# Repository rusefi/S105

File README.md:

# S105

Reverse engineering of SOATE S105 396200-3763010-00 ECU using KiCad EDA

[TL,DR: schematics (see open issues)](hardware/s105/s105.pdf)

[Interactive Pinout](https://rusefi.com/docs/pinouts/s105/)

Geehy apm32F407VGT7

[Forum Discussion](https://rusefi.com/forum/viewtopic.php?f=4&t=2496)

https://www.youtube.com/watch?v=v7S3eSeuTio

Alternative unofficial firmware https://github.com/rusefi/rusefi/tree/master/firmware/config/boards/s105

Binary https://rusefi.com/build_server/rusefi_bundle_s105.zip

See also https://github.com/rusefi/m74.9

[rusefi-status.md](rusefi-status.md)

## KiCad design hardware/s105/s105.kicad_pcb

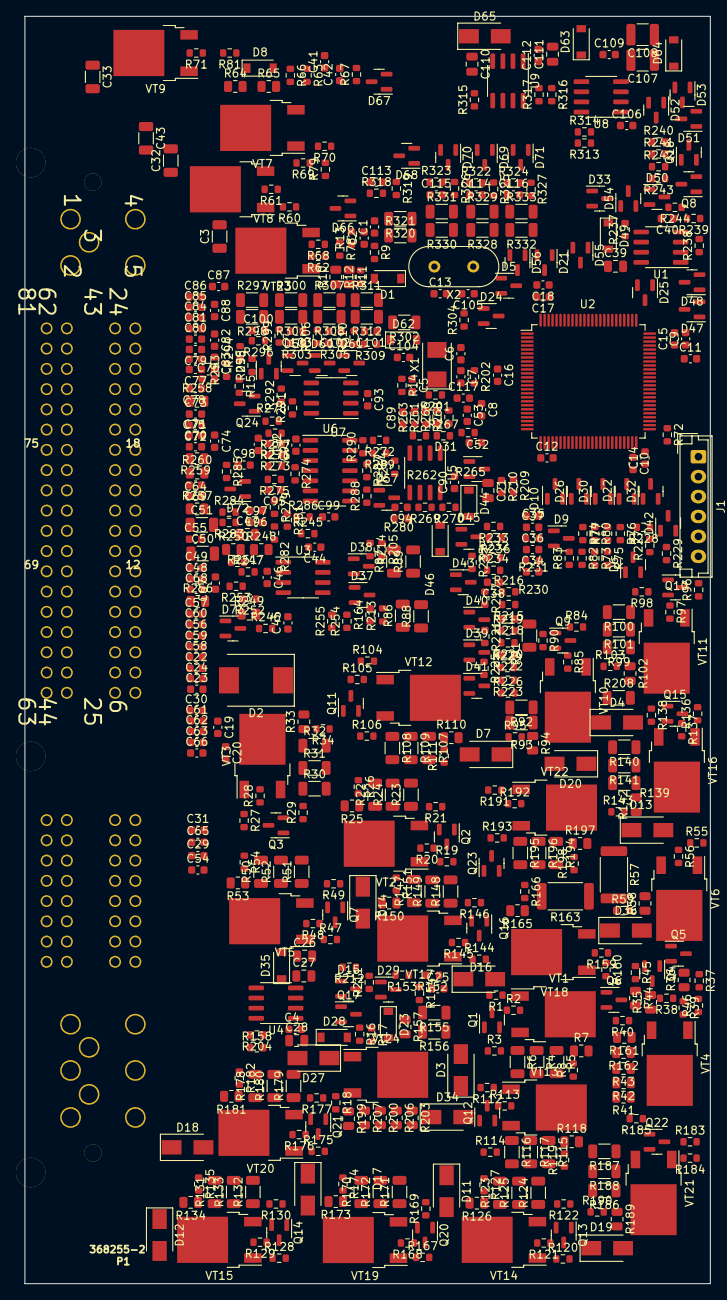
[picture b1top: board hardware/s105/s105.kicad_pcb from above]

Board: 2 copper layers, 86.0 x 159.0 mm, 583 parts (0 on the bottom side), 262 nets, no tracks yet.

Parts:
C1, C2, C41, C42: C_0603_1608Metric
C3, C32, C33, C43: C_Small; C_1206_3216Metric
C4, C19, C20, C22, C23, C24, C25, C29, C30, C31, C40, C44, C45, C46, C49, C54, C55, C56, C57, C58, C59, C60, C61, C62, C63, C64, C65, C66, C67, C68, C70, C71, C84, C85, C86, C87, C89, C90, C91, C92, C93, C94, C95, C96, C97, C98, C99, C100, C106, C109, C112: C0603; C_0603_1608Metric
C5: 10nF; C_0603_1608Metric
C6, C7: 18pF; C_0603_1608Metric
C8, C12: 1uF; C_0603_1608Metric
C9, C14, C15, C16, C17, C18, C34, C35, C36, C37, C38, C48, C52, C53, C69, C72, C73, C74, C75, C76, C77, C78, C79, C80, C81, C82, C83, C88, C101, C104, C113, C114, C115, C116, C117: 100nF; C_0603_1608Metric
C10, C11: 2.2uF; C_0603_1608Metric
C13, C102, C103, C105: NM; C_0603_1608Metric
C21, C26, C27, C28, C39, C47, C110, C111: C0805; C_0805_2012Metric
C50, C51: C1206; C_1206_3216Metric
C107, C108: C1210; C_1210_3225Metric
D1, D8, D23, D28, D44, D46: 1N4148W; D_SOD-123
D2: .; D_SMC
D3: NM; D_SMA
D4, D7, D11, D12, D13, D14, D16, D17, D18, D19, D20, D27, D34, D36, D65: .; D_SMA
D5, D6, D9, D10, D15, D21, D22, D24, D25, D26, D29, D30, D31, D32, D33, D37, D38, D39, D40, D41, D42, D43, D45, D47, D48, D50, D51, D52, D53, D54, D55, D56, D57, D58, D59, D60, D61, D66, D67, D68, D69, D70, D71, D72: BAV99; SOT-23
D35, D49, D63, D64: .; D_SOD-123
D62: NM; D_SOD-123
D73: .; SOT-23
J1: Conn_01x06; JST_EH_B6B-EH-A_1x06_P2.50mm_Vertical
P1: 368255-2
Q1, Q2, Q3, Q6, Q7, Q8, Q9, Q10, Q11, Q12, Q13, Q14, Q15, Q16, Q17, Q18, Q20, Q21, Q22, Q23: BC847C; SOT-23
Q4, Q5, Q24: .; SOT-23
R1, R2, R12, R16, R17, R19, R20, R27, R28, R37, R39, R46, R47, R48, R55, R56, R66, R84, R85, R96, R97, R104, R105, R112, R113, R120, R121, R128, R129, R136, R137, R144, R145, R159, R160, R167, R168, R175, R176, R183, R184, R191, R192: 3K; R_0603_1608Metric
R3, R18, R21, R29, R40, R49, R90, R98, R106, R114, R122, R130, R138, R146, R169, R177, R185, R193: 360R; R_0603_1608Metric
R4, R5, R6, R22, R23, R24, R30, R31, R32, R50, R51, R52, R91, R92, R93, R99, R100, R101, R107, R108, R109, R115, R116, R117, R123, R124, R125, R131, R132, R133, R139, R140, R141, R147, R148, R149, R170, R171, R172, R178, R179, R180, R186, R187, R188, R194, R195, R196: 1R; R_1206_3216Metric
R7, R25, R33, R44, R53, R58, R94, R102, R110, R118, R126, R134, R142, R150, R165, R173, R181, R189, R197: 82K; R_0805_2012Metric
R8, R15, R26, R34, R45, R54, R59, R95, R103, R111, R119, R127, R135, R143, R151, R166, R174, R182, R190, R198: 51K; R_0603_1608Metric
R9, R63: 8K2; R_0603_1608Metric
R10, R11, R64, R65: 10K; R_0805_2012Metric
R13, R67: 6K8; R_0603_1608Metric
R14: 10K; R_0603_1608Metric
R35: 6.8k; R_0805_2012Metric
R36: 2.2k; R_0805_2012Metric
R38: 18K; R_0603_1608Metric
R41, R42, R43, R161, R162, R199, R200, R203, R206, R207: 10R; R_0805_2012Metric
R57, R163: 50k?; R_2512_6332Metric
R60, R62, R69, R78, R79, R81: 10; R_0603_1608Metric
R61, R71, R80, R153, R204, R233, R236: 100; R_0603_1608Metric
R68, R70, R73, R74, R75, R82, R83, R212, R216, R219, R223, R224, R225, R226, R227, R228, R229, R232, R234, R235, R238, R255, R261, R293, R299, R304, R306, R313, R314, R326: NM; R_0603_1608Metric
R72, R211, R215, R220, R269, R272, R273, R276, R278, R279, R317: 1k; R_0603_1608Metric
R76: 22K; R_0603_1608Metric
R77: 510K; R_0603_1608Metric
R86, R87, R88, R89: 3k; R_1206_3216Metric
R152, R210: 6.8k; R_0603_1608Metric
R154, R209: 68k; R_0603_1608Metric
R155, R156, R208, R298, R311, R320, R329, R332: 4.7k; R_1206_3216Metric
R157, R248, R249, R250: 10k; R_0805_2012Metric
R158, R239, R245, R247, R251, R252, R253, R254, R295, R315, R316: 4.7k; R_0603_1608Metric
R164, R205, R213, R214, R217, R221, R237, R274, R275, R277, R285, R286, R287, R288, R289, R290: 22k; R_0603_1608Metric
R201, R230, R231, R263: 3k; R_0603_1608Metric
R202, R264, R280, R283, R303, R305, R323: 300; R_0603_1608Metric
R218, R222, R271: 6k; R_0603_1608Metric
R240, R241: 47; R_0603_1608Metric
R242, R284, R294, R310, R319, R325, R327: 51k; R_0603_1608Metric
R243, R244, R296, R309, R318, R322, R324: 33k; R_0603_1608Metric
R246: 82k; R_0603_1608Metric
R256, R257, R258, R259, R260: 0; R_0805_2012Metric
R262, R265, R266, R267, R268, R270: MN; R_0603_1608Metric
R281, R282: 18k; R_0603_1608Metric
R291, R292: 62; R_0603_1608Metric
R297, R300, R301, R302, R307, R308, R312, R321, R328, R330, R331, R333: NM; R_1206_3216Metric
U1, U4, U5, U8, U9: case only; SOIC-8_3.9x4.9mm_P1.27mm
U2: STM32F427VGT6; LQFP-100_14x14mm_P0.5mm
U3: LM2903; SOIC-8_3.9x4.9mm_P1.27mm
U6: LM2902; SO-14_3.9x8.65mm_P1.27mm
U7: SIT1042T/3; SOIC-8_3.9x4.9mm_P1.27mm
VT1, VT2, VT3, VT4, VT5, VT6, VT10, VT11, VT12, VT13, VT14, VT15, VT16, VT17, VT18, VT19, VT20, VT21, VT22, VT24: IRLR3110Z; TO-252-2
VT7, VT8, VT9, VT23: ISL9V3040D3S; TO-252-2
X1: 8MHz 20pF; Crystal_SMD_5032-2Pin_5.0x3.2mm
X2: NM; Crystal_HC49-U_Vertical

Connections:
+3.3V: C8.2, C9.2, C12.2, C14.2, C15.2, C16.2, C17.2, C18.2, C106.1, C107.1, C108.1, D5.2 (A), D6.2 (A), D9.2 (A), D10.2 (A), D21.2 (A), D22.2 (A), D24.2 (A), D25.2 (A), D26.2 (A), D29.2 (A), D30.2 (A), D31.2 (A), D32.2 (A), D33.2 (A), D37.2 (A), D38.2 (A), D39.2 (A), D40.2 (A), D41.2 (A), D42.2 (A), D43.2 (A), D44.1 (K), D45.2 (A), D46.1 (K), D47.2 (A), D48.2 (A), D50.2 (A), D51.2 (A), D52.2 (A), D53.2 (A), D54.2 (A), D55.2 (A), D56.2 (A), D58.2 (A), D59.2 (A), D60.2 (A), D61.2 (A), D64.1 (K), D66.2 (A), D67.2 (A), D68.2 (A), D69.2 (A), D70.2 (A), D71.2 (A), J1.4, R14.1, R86.2, R87.1, R88.2, R89.1, R229.2, R244.2, R265.1, R270.1, R313.1, U2.11 (VDD), U2.19 (VDD), U2.21 (VREF+), U2.22 (VDDA), U2.28 (VDD), U2.50 (VDD), U2.75 (VDD), U2.100 (VDD), U7.5 (VREF), U8.1 (BOOT)
+5V: C4.1, C28.1, C40.1, C44.1, C90.1, C93.1, D27.2 (A), D72.2 (A), R1.2, R19.2, R27.2, R46.1, R47.2, R55.2, R60.1, R78.1, R79.1, R81.1, R84.2, R96.2, R104.2, R112.2, R120.2, R128.2, R136.2, R144.2, R154.2, R155.2, R156.2, R157.2, R158.2, R159.2, R167.2, R175.2, R183.2, R191.2, R238.2, R245.2, R251.1, R271.2, R274.1, U1.3 (GND), U3.8 (V+), U4.1 (BOOT), U5.8 (PHASE), U6.4 (V+), U7.3 (VCC)
+5VD: C87.1, C111.1, C112.1, P1.32, P1.33, R74.1, R80.1, R216.2, R219.2, R224.2, R232.2, R236.1, R316.1, U9.1 (BOOT)
+12V: C19.1, C20.1, C26.1, C39.1, D1.1 (K), D2.2 (A), D3.2 (A), D4.1 (K), D7.1 (K), D8.1 (K), D11.1 (K), D12.1 (K), D13.1 (K), D14.1 (K), D16.1 (K), D17.1 (K), D18.1 (K), D19.1 (K), D20.1 (K), D35.2 (A), D36.1 (K), D49.2 (A), D63.2 (A), D65.2 (A), P1.44, P1.45, P1.63, R208.1, R297.2, R300.2, R307.2, R311.2, R320.2, R328.2, R330.2, R332.2, U1.7 (COMP/DIS/OC)
/AC_Press: C76.2, P1.21, R223.2, R224.1, R225.1
/AC_Relay: C66.1, D18.2 (A), P1.69, R181.2, VT20.2 (D)
/AFR_1: C70.1, P1.18, R76.1, R77.2, R228.2
/AFR_1_Heater: C29.1, D16.2 (A), P1.48, R165.2, VT18.2 (D)
/AFR_2: C64.1, P1.55, R82.2, R83.1, R227.1
/Absorber: C63.1, D14.2 (A), P1.46, R150.2, VT17.2 (D)
/Atart_dis_Relay: C62.1, D13.2 (A), P1.50, R142.2, VT16.2 (D)
/BOOT0: R15.1, R293.1, U2.94 (BOOT0)
/CAM_in: C88.2, P1.79, R299.2, R300.1, R301.2
/CAN_H: C84.1, P1.62, Q24.1 (B), R291.1, U7.7 (CANH)
/CAN_L: C85.1, P1.81, Q24.2 (E), R292.2, U7.6 (CANL)
/CEL: C68.1, D20.2 (A), P1.31, R197.2, VT22.2 (D)
/CLT: C75.2, P1.39, R87.2, R89.2, R205.1, R214.1
/Crank_Sens+: C47.1, C51.1, P1.15, R249.1, R250.1
/Crank_Sens-: C47.2, C50.1, P1.34, R248.1, R250.2
/DCNS: C73.2, P1.75, R306.2, R307.1, R308.2
/DIN1: C80.2, P1.72, R319.2, R320.1, R321.2
/DIN5: C83.2, P1.76, R327.2, R332.1, R333.2
/DPH2: C81.2, P1.73, R326.2, R330.1, R331.2
/ECO/CLT_Out: C57.1, D4.2 (A), P1.10, R102.2, R208.2, VT11.2 (D)
/Fan_Relay_1: C65.1, D17.2 (A), P1.68, R173.2, VT19.2 (D)
/Fan_relay_2/Unk_Out_2: C67.1, D19.2 (A), P1.30, R189.2, VT21.2 (D)
/Fuel_Pump_Relay: C61.1, D12.2 (A), P1.70, R134.2, VT15.2 (D)
/GNDA: P1.17, P1.20, P1.35, P1.36, P1.51, P1.52, P1.53, P1.54, R256.1, R257.1, R258.1, R259.1, R260.1
/IAT: C77.2, P1.40, R86.1, R88.1, R164.1, R213.1
/IGN_1: C3.1, P1.5, R10.1, VT23.2 (C)
/IGN_2: C43.1, P1.2, R64.1, VT7.2 (C)
/IGN_3: C32.1, P1.4, VT8.2 (C)
/IGN_4: C33.1, P1.1, VT9.2 (C)
/IGN_swt: C49.1, D28.1 (K), P1.13
/INJ_1: C22.1, P1.27, R7.2, VT1.2 (D)
/INJ_2: C23.1, P1.6, R25.2, VT2.2 (D)
/INJ_3: C24.1, P1.7, R33.2, VT3.2 (D)
/INJ_4: C54.1, P1.47, R53.2, VT5.2 (D)
/INJ_6/AFR_2_Heater: C31.1, D36.2 (A), P1.49, R58.2, VT6.2 (D)
/INJ_7: C30.1, P1.25, R35.1, R44.2, VT4.2 (D)
/Idle_valve_close: C59.1, P1.28, R118.2, VT13.2 (D)
/Idle_valve_open: C60.1, D11.2 (A), P1.29, R126.2, VT14.2 (D)
/K-line: C86.1, P1.71, R237.1, R240.1, R241.1, R242.1, U1.6 (FB)
/Knock: C71.1, C98.2, P1.19
/MAF: C72.2, P1.37, R232.1, R234.1, R235.1
/MAP: C74.2, P1.56, R215.2, R216.1, R217.1
/MCU/5V: J1.5, R254.1
/NEW_PIN: C48.2, P1.12, R302.2
/OD 2A15/OUT2: R163.1, VT18.3 (S)
/OD 2A24/IN: R57.1, R268.2, VT6.3 (S)
/PA0: C53.2, D40.3 (K), R217.2, R218.2, U2.23 (PA0)
/PA1: C52.2, D39.3 (K), R221.2, R222.2, U2.24 (PA1)
/PA2: C92.1, D46.2 (A), R278.1, U2.25 (PA2)
/PA3: C36.2, D38.3 (K), R214.2, U2.26 (PA3)
/PA5: C89.1, R261.1, R262.2, R263.1, R264.2, U2.30 (PA5)
/PA6: D41.3 (K), R225.2, R226.1, R231.1, U2.31 (PA6)
/PA7: C37.2, D6.3 (K), R76.2, U2.32 (PA7)
/PA8: D53.3 (K), R102.1, R103.2, U2.67 (PA8)
/PA9: R239.2, U1.4 (LGATE), U2.68 (PA9)
/PA10: D50.3 (K), R242.2, R243.1, U1.1 (BOOT), U2.69 (PA10)
/PA11: U2.70 (PA11), U7.4 (RXD)
/PA12: U2.71 (PA12), U7.1 (TXD)
/PA13: J1.1, U2.72 (PA13)
/PA14: J1.3, U2.76 (PA14)
/PA15: D25.3 (K), R58.1, R59.2, U2.77 (PA15)
/PB0: C34.2, U2.35 (PB0)
/PB1: C21.1, D31.3 (K), R209.1, R210.1, U2.36 (PB1)
/PB2: R254.2, R255.1, U2.37 (PB2)
/PB3: C101.2, D61.3 (K), R309.2, R310.1, U2.89 (PB3)
/PB4: R315.1, U2.90 (PB4), U4.5 (VCC), U9.5 (VCC)
/PB5: D55.3 (K), R126.1, R127.2, U2.91 (PB5)
/PB6: D33.3 (K), R118.1, R119.2, U2.92 (PB6)
/PB7: D21.3 (K), R110.1, R111.2, U2.93 (PB7)
/PB8: Q11.3 (C), R104.1, R105.1, U2.95 (PB8)
/PB9: Q10.3 (C), R96.1, R97.1, U2.96 (PB9)
/PB10: D30.3 (K), U2.47 (PB10), U3.1
/PB11: C103.2, D59.3 (K), R299.1, R303.2, U2.48 (PB11)
/PB12: D32.3 (K), R33.1, R34.2, U2.51 (PB12)
/PB13: D42.3 (K), R53.1, R54.2, U2.52 (PB13)
/PB14: Q16.3 (C), R144.1, R145.1, U2.53 (PB14)
/PB15: R72.1, U2.54 (PB15)
/PC0: C117.2, D44.2 (A), D45.3 (K), R233.2, R236.2, U2.15 (PC0)
/PC1: C38.2, D43.3 (K), R201.1, R235.2, U2.16 (PC1)
/PC2: C41.1, R63.1, U2.17 (PC2)
/PC3: C1.1, R9.1, U2.18 (PC3)
/PC4: C35.2, D37.3 (K), R164.2, U2.33 (PC4)
/PC5: D9.3 (K), R83.2, R230.1, U2.34 (PC5)
/PC6: Q13.3 (C), R120.1, R121.1, U2.63 (PC6)
/PC7: Q12.3 (C), R112.1, R113.1, U2.64 (PC7)
/PC8: D47.3 (K), R7.1, R8.2, U2.65 (PC8)
/PC9: D48.3 (K), R25.1, R26.2, U2.66 (PC9)
/PC10: C116.2, D71.3 (K), R324.2, R327.1, U2.78 (PC10)
/PC11: C115.2, D70.3 (K), R323.2, R326.1, U2.79 (PC11)
/PC12: C113.2, D68.3 (K), R318.2, R319.1, U2.80 (PC12)
/PC13: C102.2, D60.3 (K), R305.2, R306.1, U2.7 (PC13)
/PD0: R37.2, R46.2, U2.81 (PD0)
/PD1: D51.3 (K), R44.1, R45.2, U2.82 (PD1)
/PD2: Q14.3 (C), R128.1, R129.1, U2.83 (PD2)
/PD3: D52.3 (K), R134.1, R135.2, U2.84 (PD3)
/PD4: C114.2, D69.3 (K), R322.2, R325.1, U2.85 (PD4)
/PD5: R295.1, U2.86 (PD5)
/PD6: Q20.3 (C), R167.1, R168.1, U2.87 (PD6)
/PD7: D54.3 (K), R173.1, R174.2, U2.88 (PD7)
/PD9: Q2.3 (C), R19.1, R20.1, U2.56 (PD9)
/PD10: Q3.3 (C), R27.1, R28.1, U2.57 (PD10)
/PD11: Q7.3 (C), R47.1, R48.1, U2.58 (PD11)
/PD12: R69.1, R79.2, U2.59 (PD12)
/PD13: R62.1, R78.2, U2.60 (PD13)
/PD14: R71.1, R81.2, U2.61 (PD14)
/PD15: R60.2, R61.1, U2.62 (PD15)
/PE0: Q9.3 (C), R84.1, R85.1, U2.97 (PE0)
/PE1: D56.3 (K), R94.1, R95.2, U2.98 (PE1)
/PE2: D5.3 (K), R165.1, R166.2, U2.1 (PE2)
/PE3: D24.3 (K), R150.1, R151.2, U2.2 (PE3)
/PE4: D72.3 (K), R284.1, R285.2, U2.3 (PE4)
/PE5: R159.1, R160.1, R269.1, R270.2, U2.4 (PE5), U5.7 (COMP/DIS/OC)
/PE6: Q1.3 (C), R1.1, R2.1, R55.1, R56.1, R265.2, R267.2, U2.5 (PE6), U5.1 (BOOT)
/PE7: R227.2, R228.1, R229.1, U2.38 (PE7)
/PE8: Q22.3 (C), R183.1, R184.1, U2.39 (PE8)
/PE9: D26.3 (K), R189.1, R190.2, U2.40 (PE9)
/PE10: Q21.3 (C), R175.1, R176.1, U2.41 (PE10)
/PE11: D10.3 (K), R181.1, R182.2, U2.42 (PE11)
/PE12: Q15.3 (C), R136.1, R137.1, U2.43 (PE12)
/PE13: R142.1, R143.2, U2.44 (PE13)
/PE14: Q23.3 (C), R191.1, R192.1, U2.45 (PE14)
/PE15: D22.3 (K), R197.1, R198.2, U2.46 (PE15)
/Prog_mode: C79.2, P1.43, R293.2, R294.2, R297.1, R298.2
/Speed_in: C78.2, P1.59, R310.2, R311.1, R312.2
/Start_req: C82.2, P1.77, R325.2, R328.1, R329.2
/TACH: C58.1, D7.2 (A), P1.8, R110.2, VT12.2 (D)
/TPS: C69.2, P1.16, R219.1, R220.2, R221.1
/Unk_Out_1: C56.1, P1.9, R94.2, VT10.2 (D)
/VBAT: C104.2, D62.2 (A), R302.1, U2.6 (VBAT)
GND: C1.2, C2.2, C3.2, C4.2, C5.1, C6.2, C7.2, C8.1, C9.1, C10.2, C11.2, C12.1, C13.2, C14.1, C15.1, C16.1, C17.1, C18.1, C19.2, C20.2, C21.2, C22.2, C23.2, C24.2, C25.2, C26.2, C27.2, C28.2, C29.2, C30.2, C31.2, C32.2, C33.2, C34.1, C35.1, C36.1, C37.1, C38.1, C39.2, C40.2, C41.2, C42.2, C43.2, C44.2, C45.2, C48.1, C49.2, C50.2, C51.2, C52.1, C53.1, C54.2, C55.2, C56.2, C57.2, C58.2, C59.2, C60.2, C61.2, C62.2, C63.2, C64.2, C65.2, C66.2, C67.2, C68.2, C69.1, C70.2, C71.2, C72.1, C73.1, C74.1, C75.1, C76.1, C77.1, C78.1, C79.1, C80.1, C81.1, C82.1, C83.1, C84.2, C85.2, C86.2, C87.2, C88.1, C89.2, C90.2, C92.2, C93.2, C94.2, C95.2, C100.2, C101.1, C102.1, C103.1, C104.1, C105.2, C106.2, C107.2, C108.2, C109.2, C110.2, C111.2, C112.2, C113.1, C114.1, C115.1, C116.1, C117.1, D2.1 (K), D5.1 (K), D6.1 (K), D9.1 (K), D10.1 (K), D15.1 (K), D21.1 (K), D22.1 (K), D24.1 (K), D25.1 (K), D26.1 (K), D27.1 (K), D29.1 (K), D30.1 (K), D31.1 (K), D32.1 (K), D33.1 (K), D37.1 (K), D38.1 (K), D39.1 (K), D40.1 (K), D41.1 (K), D42.1 (K), D43.1 (K), D45.1 (K), D47.1 (K), D48.1 (K), D50.1 (K), D51.1 (K), D52.1 (K), D53.1 (K), D54.1 (K), D55.1 (K), D56.1 (K), D58.1 (K), D59.1 (K), D60.1 (K), D61.1 (K), D62.1 (K), D64.2 (A), D66.1 (K), D67.1 (K), D68.1 (K), D69.1 (K), D70.1 (K), D71.1 (K), D72.1 (K), J1.2, P1.3, P1.61, P1.80, Q1.2 (E), Q2.2 (E), Q3.2 (E), Q5.2 (E), Q6.2 (E), Q7.2 (E), Q8.2 (E), Q9.2 (E), Q10.2 (E), Q11.2 (E), Q12.2 (E), Q13.2 (E), Q14.2 (E), Q15.2 (E), Q16.2 (E), Q17.2 (E), Q18.2 (E), Q20.2 (E), Q21.2 (E), Q22.2 (E), Q23.2 (E), Q24.3 (C), R4.2, R5.2, R6.2, R8.1, R13.2, R15.2, R22.2, R23.2, R24.2, R26.1, R30.2, R31.2, R32.2, R34.1, R41.2, R42.2, R43.2, R45.1, R50.2, R51.2, R52.2, R54.1, R57.2, R59.1, R67.2, R68.1, R70.1, R72.2, R73.2, R75.2, R91.2, R92.2, R93.2, R95.1, R99.2, R100.2, R101.2, R103.1, R107.2, R108.2, R109.2, R111.1, R115.2, R116.2, R117.2, R119.1, R123.2, R124.2, R125.2, R127.1, R131.2, R132.2, R133.2, R135.1, R139.2, R140.2, R141.2, R143.1, R147.2, R148.2, R149.2, R151.1, R152.1, R155.1, R156.1, R161.2, R162.2, R163.2, R166.1, R170.2, R171.2, R172.2, R174.1, R178.2, R179.2, R180.2, R182.1, R186.2, R187.2, R188.2, R190.1, R194.2, R195.2, R196.2, R198.1, R199.2, R200.2, R201.2, R203.2, R204.1, R205.2, R206.2, R207.2, R209.2, R210.2, R211.2, R212.2, R213.2, R215.1, R218.1, R220.1, R222.1, R223.1, R226.2, R230.2, R231.2, R233.1, R234.2, R243.2, R253.2, R255.2, R256.2, R257.2, R258.2, R259.2, R260.2, R261.2, R263.2, R266.2, R275.2, R280.2, R283.2, R296.1, R298.1, R301.1, R303.1, R305.1, R308.1, R309.1, R312.1, R314.2, R315.2, R317.2, R318.1, R321.1, R322.1, R323.1, R324.1, R329.1, R331.1, R333.1, U1.5 (VCC), U1.8 (PHASE), U2.10 (VSS), U2.20 (VSSA), U2.27 (VSS), U2.74 (VSS), U2.99 (VSS), U3.4 (V-), U4.2 (UGATE), U4.3 (GND), U5.4 (LGATE), U6.11 (V-), U7.2 (GND), U7.8 (S), U8.2 (UGATE), U8.3 (GND), U9.2 (UGATE), U9.3 (GND), VT7.3 (E), VT8.3 (E), VT9.3 (E), VT23.3 (E)
unnamed: C2.1, D66.3 (K), R9.2, R12.2, R13.1
unnamed: C5.2, R14.2, U2.14 (NRST)
unnamed: C6.1, U2.12 (PH0), X1.2
unnamed: C7.1, R202.1, X1.1
unnamed: C10.1, U2.49 (VCAP_1)
unnamed: C11.1, U2.73 (VCAP_2)
unnamed: C13.1, R304.2, X2.1
unnamed: C25.1, R152.2, R153.1, R154.1
unnamed: C27.1, D35.1 (K), U4.4 (LGATE)
unnamed: C42.1, D67.3 (K), R63.2, R66.2, R67.1
unnamed: C45.1, R245.1, R246.2
unnamed: C46.1, D73.1 (K), R247.2, R248.2, U3.2 (-)
unnamed: C46.2, D73.3 (K), R246.1, R249.2, R252.1, U3.3 (+)
unnamed: C55.1, P1.14
unnamed: C91.1, R272.1, R273.1, R276.1, U6.2 (-)
unnamed: C91.2, R277.1, R278.2, U6.1
unnamed: C94.1, R269.2, R280.1, U5.6 (FB)
unnamed: C95.1, R274.2, R275.1, U6.3 (+), U6.5 (+), U6.10 (+)
unnamed: C96.1, R279.1, U6.6 (-)
unnamed: C96.2, C97.1, R283.1, R284.2
unnamed: C97.2, R282.2, R286.1, U6.7
unnamed: C98.1, R285.1
unnamed: C99.1, R286.2
unnamed: C99.2, R287.2, R288.2, U6.9 (-)
unnamed: C100.1, D58.3 (K), R294.1, R295.2, R296.2
unnamed: C105.1, U2.8 (PC14), X2.2
unnamed: C109.1, D63.1 (K), U8.4 (LGATE), U8.5 (VCC)
unnamed: C110.1, D65.1 (K), U9.4 (LGATE)
unnamed: D1.2 (A), R11.2, R12.1
unnamed: D3.1 (K), D34.2 (A)
unnamed: D8.2 (A), R65.2, R66.1
unnamed: D15.3 (K), D23.2 (A), Q17.3 (C), R16.1, R17.1, R211.1, R212.1
unnamed: D23.1 (K), R157.1
unnamed: D28.2 (A), R16.2
unnamed: D29.3 (K), R153.2
unnamed: D34.1 (K), VT24.2 (D)
unnamed: D49.1 (K), R237.2
unnamed: D57.1 (K), R287.1, U6.12 (+)
unnamed: D57.2 (A), R288.1, R289.1
unnamed: D57.3 (K), U6.8
unnamed: Q1.1 (B), R3.1
unnamed: Q2.1 (B), R21.1
unnamed: Q3.1 (B), R29.1
unnamed: Q4.1 (B), Q6.3 (C), R36.1, R38.1, R39.1
unnamed: Q4.3 (C), R35.2, R38.2
unnamed: Q5.1 (B), R37.1
unnamed: Q5.3 (C), R36.2
unnamed: Q6.1 (B), R40.1
unnamed: Q7.1 (B), R49.1
unnamed: Q8.1 (B), R239.1
unnamed: Q9.1 (B), R90.1
unnamed: Q10.1 (B), R98.1
unnamed: Q11.1 (B), R106.1
unnamed: Q12.1 (B), R114.1
unnamed: Q13.1 (B), R122.1
unnamed: Q14.1 (B), R130.1
unnamed: Q15.1 (B), R138.1
unnamed: Q16.1 (B), R146.1
unnamed: Q17.1 (B), R18.1
unnamed: Q8.3 (C), Q18.1 (B), R244.1
unnamed: Q18.3 (C), R240.2, R241.2
unnamed: Q20.1 (B), R169.1
unnamed: Q21.1 (B), R177.1
unnamed: Q22.1 (B), R185.1
unnamed: Q23.1 (B), R193.1
unnamed: R2.2, VT1.1 (G)
unnamed: R3.2, R4.1, R5.1, R6.1, VT1.3 (S)
unnamed: R10.2, R11.1
unnamed: R17.2, VT24.1 (G)
unnamed: R18.2, R199.1, R200.1, R203.1, R206.1, R207.1, VT24.3 (S)
unnamed: R20.2, VT2.1 (G)
unnamed: R21.2, R22.1, R23.1, R24.1, VT2.3 (S)
unnamed: R28.2, VT3.1 (G)
unnamed: R29.2, R30.1, R31.1, R32.1, VT3.3 (S)
unnamed: R39.2, VT4.1 (G)
unnamed: R48.2, VT5.1 (G)
unnamed: R49.2, R50.1, R51.1, R52.1, VT5.3 (S)
unnamed: R56.2, VT6.1 (G)
unnamed: R61.2, VT8.1 (G)
unnamed: R62.2, R68.2, VT23.1 (G)
unnamed: R64.2, R65.1
unnamed: R69.2, R70.2, VT7.1 (G)
unnamed: R71.2, VT9.1 (G)
unnamed: R73.1, R74.2, R82.1
unnamed: R75.1, R77.1, R80.2
unnamed: R85.2, VT10.1 (G)
unnamed: R90.2, R91.1, R92.1, R93.1, VT10.3 (S)
unnamed: R97.2, VT11.1 (G)
unnamed: R98.2, R99.1, R100.1, R101.1, VT11.3 (S)
unnamed: R105.2, VT12.1 (G)
unnamed: R106.2, R107.1, R108.1, R109.1, VT12.3 (S)
unnamed: R113.2, VT13.1 (G)
unnamed: R114.2, R115.1, R116.1, R117.1, VT13.3 (S)
unnamed: R121.2, VT14.1 (G)
unnamed: R122.2, R123.1, R124.1, R125.1, VT14.3 (S)
unnamed: R129.2, VT15.1 (G)
unnamed: R130.2, R131.1, R132.1, R133.1, VT15.3 (S)
unnamed: R137.2, VT16.1 (G)
unnamed: R138.2, R139.1, R140.1, R141.1, VT16.3 (S)
unnamed: R145.2, VT17.1 (G)
unnamed: R146.2, R147.1, R148.1, R149.1, VT17.3 (S)
unnamed: R158.1, R204.2, U4.8 (PHASE)
unnamed: R160.2, VT18.1 (G)
unnamed: R40.2, R41.1, R42.1, R43.1, R161.1, R162.1, VT4.3 (S)
unnamed: R168.2, VT19.1 (G)
unnamed: R169.2, R170.1, R171.1, R172.1, VT19.3 (S)
unnamed: R176.2, VT20.1 (G)
unnamed: R177.2, R178.1, R179.1, R180.1, VT20.3 (S)
unnamed: R184.2, VT21.1 (G)
unnamed: R185.2, R186.1, R187.1, R188.1, VT21.3 (S)
unnamed: R192.2, VT22.1 (G)
unnamed: R193.2, R194.1, R195.1, R196.1, VT22.3 (S)
unnamed: R202.2, U2.13 (PH1)
unnamed: R238.1, U1.2 (UGATE)
unnamed: R247.1, R251.2, R252.2, R253.1
unnamed: R262.1, U5.3 (GND)
unnamed: R264.1, U5.5 (VCC)
unnamed: R266.1, R267.1, R268.1, U5.2 (UGATE)
unnamed: R271.1, R273.2
unnamed: R272.2, R290.2, U6.14
unnamed: R276.2, R277.2
unnamed: R279.2, R281.1
unnamed: R281.2, R282.1
unnamed: R289.2, R290.1, U6.13 (-)
unnamed: R291.2, R292.1
unnamed: R304.1, U2.9 (PC15)
unnamed: R313.2, R314.1, U8.8 (PHASE)
unnamed: R316.2, R317.1, U9.8 (PHASE)

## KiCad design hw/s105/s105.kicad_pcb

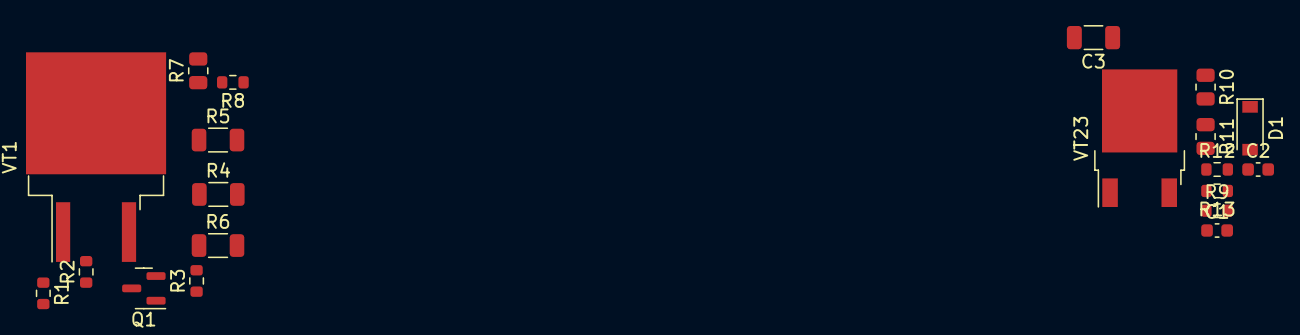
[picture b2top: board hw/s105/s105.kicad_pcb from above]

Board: 2 copper layers, 20 parts (0 on the bottom side), 13 nets, no tracks yet.

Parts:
C1, C2: C_0603_1608Metric
C3: C_Small; C_1206_3216Metric
D1: 1N4148W; D_SOD-123
Q1: BC847C; SOT-23
R1, R2, R12: 3K; R_0603_1608Metric
R3: 360R; R_0603_1608Metric
R4, R5, R6: 1R; R_1206_3216Metric
R7: 82K; R_0805_2012Metric
R8: 51K; R_0603_1608Metric
R9: 8K2; R_0603_1608Metric
R10, R11: 10K; R_0805_2012Metric
R13: 6K8; R_0603_1608Metric
VT1: IRLR3110Z; TO-263-2
VT23: ISL9V3040D3S; TO-252-2

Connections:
+5V: D1.1 (K), R1.2
/IGN driver/FB: C1.1, R9.1
/IGN driver/OUT: C3.1, R10.1, VT23.2 (C)
/OD 2A/FB: R7.1, R8.2
/OD 2A/IN: Q1.3 (C), R1.1, R2.1
/OD 2A/OUT: R7.2, VT1.2 (D)
GNDPWR: C1.2, C2.2, C3.2, Q1.2 (E), R4.2, R5.2, R6.2, R8.1, R13.2, VT23.3 (E)
unnamed: C2.1, R9.2, R12.2, R13.1
unnamed: D1.2 (A), R11.2, R12.1
unnamed: Q1.1 (B), R3.1
unnamed: R2.2, VT1.1 (G)
unnamed: R3.2, R4.1, R5.1, R6.1, VT1.3 (S)
unnamed: R10.2, R11.1

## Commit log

2022-12-30 high-res
2023-01-04 binaries
2023-01-29 S105: some reversed schematic blocks
2023-01-29 only folder rename
2023-02-07 наименование цепей разъема
2023-02-08 разместила схожие блоки
2023-02-08 git is the backup
2023-02-08 fresh
2023-02-09 вписала в габариты платы, продолжила опознание
2023-02-10 новые модули, продолжение расположения
2023-02-14 заполняем плату дальше
2023-02-15 +knock
2023-02-16 can, analog inputs
2023-02-16 закончила пока что
2023-02-21 #4 #5 #6 #8
